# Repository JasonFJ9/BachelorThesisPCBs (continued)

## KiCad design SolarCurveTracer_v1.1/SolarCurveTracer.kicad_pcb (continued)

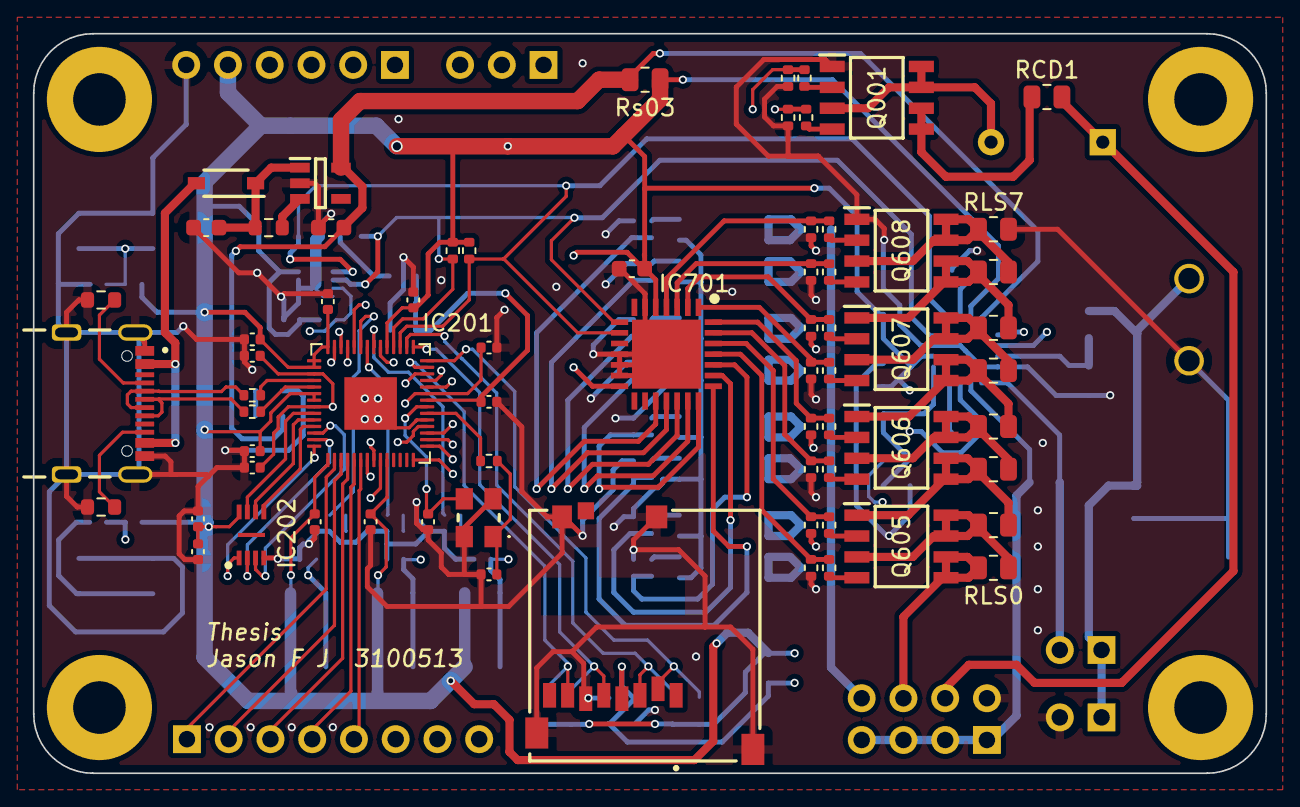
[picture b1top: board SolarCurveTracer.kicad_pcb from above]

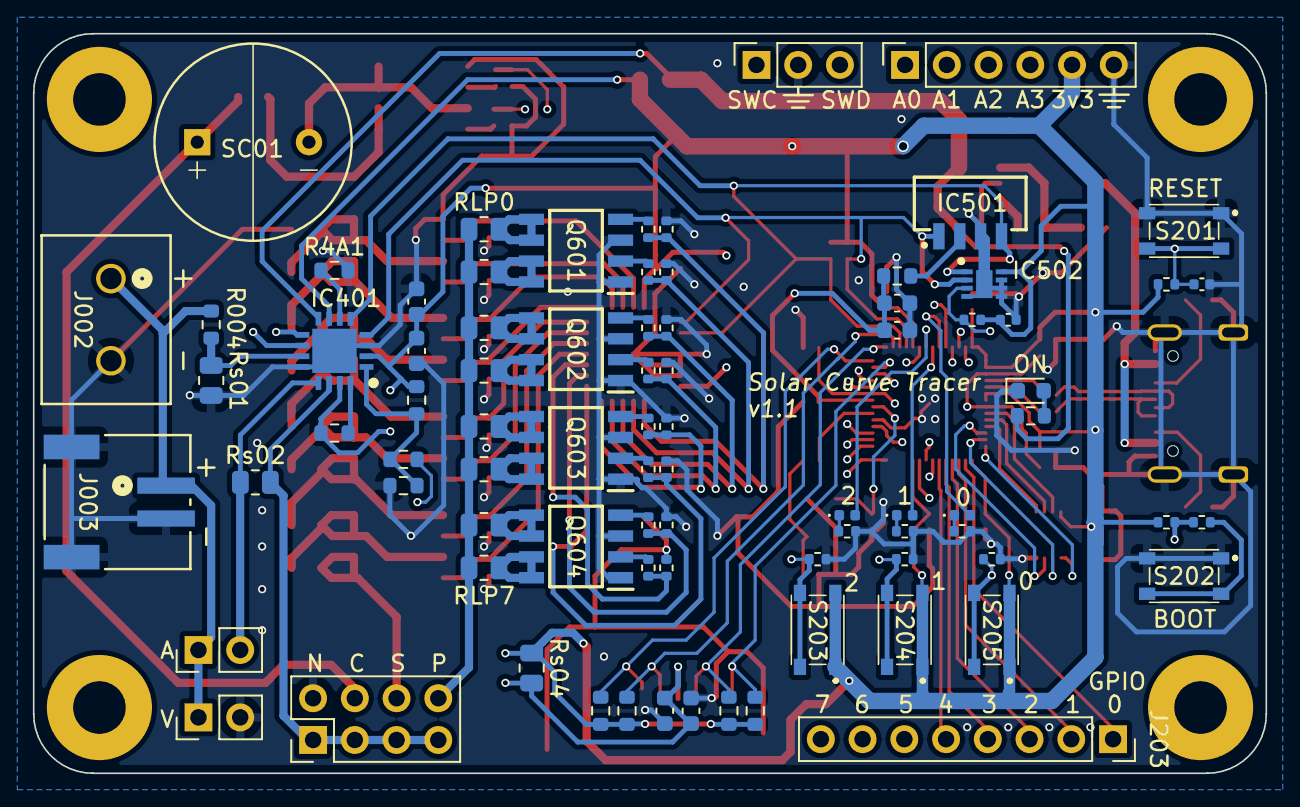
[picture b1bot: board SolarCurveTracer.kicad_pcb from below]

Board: 4 copper layers, 75.0 x 45.0 mm, 154 parts (82 on the bottom side), 120 nets.

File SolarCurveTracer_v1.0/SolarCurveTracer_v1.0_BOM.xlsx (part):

Reference | Value | Footprint | Description | Manufacturer_Part_Number | Mouser Link | DigiKey Link | Qty/Board | Qty/ X Board |  |  |  | X = | 3
AH0-AH2 | JP | Jumper:SolderJumper-2_P1.3mm_Open_TrianglePad1.0x1.5mm | No Need To Order |  | No Need To Order | No Need To Order | 0 | 0 |  |  |  |  | 3
C101, C102 | 1uF | Capacitor_SMD:C_0603_1608Metric |  |  |  |  | 2 | 6 |  |  |  |  | 3
C201, C202 | 15pF | Capacitor_SMD:C_0402_1005Metric | Low Tolerance & High Freq, Changed from 20pF to 15pF |  |  |  | 2 | 6 |  |  |  |  | 3
C203-C208, C211-C213, (C215, C503) | 0.1uF | Capacitor_SMD:C_0402_1005Metric |  |  |  |  | 11 | 33 |  |  |  |  | 3
C209, C210 | 1uF | Capacitor_SMD:C_0402_1005Metric |  |  |  |  | 2 | 6 |  |  |  |  | 3
C214 | 4.7uF | Capacitor_SMD:C_0402_1005Metric |  |  |  |  | 1 | 3 |  |  |  |  | 3
C301, C502 | 10uF | Capacitor_SMD:C_0603_1608Metric |  |  |  |  | 2 | 6 |  |  |  |  | 3
C302, C402, C501, C701 | 0.1uF | Capacitor_SMD:C_0603_1608Metric |  |  |  |  | 4 | 12 |  |  |  |  | 3
C401 | 4.7uF | Capacitor_SMD:C_0603_1608Metric |  |  |  |  | 1 | 3 |  |  |  |  | 3
D101 | B5817W-TP | B5817W-TP:SOD3716X135N |  | B5817W-TP | https://www.mouser.de/ProductDetail/833-B5817W-TP | https://www.digikey.de/en/products/detail/good-ark-semicondu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 | 1 | 3 |  |  |  |  | 3
D201-D203 | LED | LED_SMD:LED_0402_1005Metric |  |  |  |  | 3 | 9 |  |  |  |  | 3
H1-H4 | MountingHole_Pad | MountingHole:MountingHole_3.2mm_M3_Pad | No Need To Order |  | No Need To Order | No Need To Order | 0 | 0 |  |  |  |  | 3
IC101 | AP2112K-3.3TRG1 | AP2112K-3.3TRG1:SOT95P282X130-5N | Mouser Possible Long Lead time | AP2112K-3.3TRG1 | https://www.mouser.de/ProductDetail/Diodes-Incorporated/AP21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 | https://www.digikey.de/de/products/detail/diodes-incorporate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 | 1 | 3 |  |  |  |  | 3
IC201 | RP2040 | Package_DFN_QFN:QFN-56-1EP_7x7mm_P0.4mm_EP3.2x3.2mm |  |  | https://www.mouser.de/ProductDetail/Raspberry-Pi/SC091413?qs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 | https://www.digikey.de/en/products/detail/raspberry-pi/SC091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 | 1 | 3 |  |  |  |  | 3
IC202 | W25Q16JVUXIQ_TR | W25Q16JVUXIQ_TR:SON50P300X200X60-9N |  | W25Q16JVUXIQ TR | https://www.mouser.de/ProductDetail/Winbond/W25Q16JVUXIQ-TR?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 | https://www.digikey.de/en/products/detail/winbond-electronic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 | 1 | 3 |  |  |  |  | 3
IC401 | PAC1934T-I_JQ | PAC1934T-I_JQ:QFN65P400X400X55-17N-D |  | PAC1934T-I/JQ | https://www.mouser.de/ProductDetail/Microchip-Technology/PAC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 | Out of Stock | 1 | 3 |  |  |  |  | 3
IC501 | VEML7700-TT | VEML7700-TT:VEML7700 |  | VEML7700-TT | https://www.mouser.de/ProductDetail/Vishay-Semiconductors/VE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 | https://www.digikey.de/en/products/detail/vishay-semiconduct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 | 1 | 3 |  |  |  |  | 3
IC502 | TMP1075DSGR | TMP1075DSGR:SON50P200X200X80-9N |  | TMP1075DSGR | https://www.mouser.de/ProductDetail/Texas-Instruments/TMP107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 | https://www.digikey.de/en/products/detail/texas-instruments/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 | 1 | 3 |  |  |  |  | 3
IC701 | MCP23017-E_ML | MCP23017-E_ML:QFN65P600X600X100-29N-D |  | MCP23017-E/ML | https://www.mouser.de/ProductDetail/Microchip-Technology/MCP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 | https://www.digikey.de/en/products/detail/microchip-technolo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 | 1 | 3 |  |  |  |  | 3
J001 | Conn_02x04_Odd_Even | Connector_PinHeader_2.54mm:PinHeader_2x04_P2.54mm_Vertical | No Need To Order |  | No Need To Order | No Need To Order | 0 | 0 |  |  |  |  | 3
J002 | 691137710002 | 691137710002:CONN2_710002_WRE |  | 691137710002 | https://www.mouser.de/ProductDetail/Wurth-Elektronik/6911377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 | https://www.digikey.de/en/products/detail/w%C3%BCrth-elektro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 | 1 | 3 |  |  |  |  | 3
J003 | S2B-PH-SM4-TB | S2B_PH_SM4_TB:CONN_S2B-PH-SM4-TB_JST | No Need To Order (In IOT Garage) |  | No Need To Order | No Need To Order | 0 | 0 |  |  |  |  | 3
J004, J005 | Conn_01x02_Pin | Connector_PinHeader_2.54mm:PinHeader_1x02_P2.54mm_Vertical | No Need To Order |  | No Need To Order | No Need To Order | 0 | 0 |  |  |  |  | 3
J101 | USB4105-GF-A | USB4105_GF_A:GCT_USB4105-GF-A |  | USB4105-GF-A | https://www.mouser.de/ProductDetail/GCT/USB4105-GF-A?qs=KUoI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 | https://www.digikey.de/en/products/detail/gct/USB4105-GF-A/11198441 | 1 | 3 |  |  |  |  | 3
J201 | Conn_01x03_Pin | Connector_PinSocket_2.54mm:PinSocket_1x03_P2.54mm_Vertical | No Need To Order |  | No Need To Order | No Need To Order | 0 | 0 |  |  |  |  | 3
J202 | Conn_01x06_Pin | Connector_PinSocket_2.54mm:PinSocket_1x06_P2.54mm_Vertical | No Need To Order |  | No Need To Order | No Need To Order | 0 | 0 |  |  |  |  | 3
J203 | Conn_01x11_Pin | Connector_PinSocket_2.54mm:PinSocket_1x11_P2.54mm_Vertical | No Need To Order |  | No Need To Order | No Need To Order | 0 | 0 |  |  |  |  | 3
J301 | MEM2052-00-195-00-A_REVA | MEM2052-00-195-00-A_REVA:GCT_MEM2052-00-195-00-A_REVA |  | MEM2052-00-195-00-A | https://www.mouser.de/ProductDetail/GCT/MEM2052-00-195-00-A?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 | https://www.digikey.de/en/products/detail/gct/MEM2052-00-195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 | 1 | 3 |  |  |  |  | 3
ON1 | LED | LED_SMD:LED_0603_1608Metric |  |  |  |  | 1 | 3 |  |  |  |  | 3
Q1, Q601-Q608 | SI4204DY-T1-GE3 | SI4204DY-T1-GE3:SOIC127P600X175-8N |  | SI4204DY-T1-GE3 | https://www.mouser.de/ProductDetail/Vishay-Semiconductors/SI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 | https://www.digikey.de/de/products/detail/vishay-siliconix/S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 | 9 | 27 |  |  |  |  | 3
R001-R003 | 4.7kR | Resistor_SMD:R_0402_1005Metric |  |  |  |  | 3 | 9 |  |  |  |  | 3
R004 | 150kR | Resistor_SMD:R_0603_1608Metric | 0603 1% tolerance |  | https://www.mouser.de/ProductDetail/Vishay-Dale/CRCW0603150K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 |  | 1 | 3 |  |  |  |  | 3
R4A1 | 499R | Resistor_SMD:R_0603_1608Metric |  |  |  |  | 1 | 3 |  |  |  |  | 3
R005, R006, R203, R601-R608, R617-R624 | 1kR | Resistor_SMD:R_0402_1005Metric |  |  |  |  | 19 | 57 |  |  |  |  | 3
R007, R008, R209-R212, R609-R616, R625-R632, R701-R703 | 10kR | Resistor_SMD:R_0402_1005Metric |  |  |  |  | 25 | 75 |  |  |  |  | 3
R101, R102 | 5kR | Resistor_SMD:R_0603_1608Metric |  |  |  |  | 2 | 6 |  |  |  |  | 3
R103, R402, R403, R501 | 10kR | Resistor_SMD:R_0603_1608Metric |  |  |  |  | 4 | 12 |  |  |  |  | 3
R104 | 1kR | Resistor_SMD:R_0603_1608Metric |  |  |  |  | 1 | 3 |  |  |  |  | 3
R201, R202 | 27R | Resistor_SMD:R_0402_1005Metric |  |  |  |  | 2 | 6 |  |  |  |  | 3
R204-R206, (R207) | 499R | Resistor_SMD:R_0402_1005Metric |  |  |  |  | 4 | 12 |  |  |  |  | 3
R208 | 2kR | Resistor_SMD:R_0402_1005Metric |  |  |  |  | 1 | 3 |  |  |  |  | 3
R301-R304 | 47kR | Resistor_SMD:R_0603_1608Metric |  |  |  |  | 4 | 12 |  |  |  |  | 3
R404, R405 | 0R | Resistor_SMD:R_0603_1608Metric |  |  |  |  | 2 | 6 |  |  |  |  | 3
RLP4 | 68R | Resistor_SMD:R_0805_2012Metric | 0805 1% tolerance 0.5W |  | https://www.mouser.de/ProductDetail/Vishay-Dale/CRCW080568R0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 |  | 1 | 3 |  |  |  |  | 3
RLP5 | 150R | Resistor_SMD:R_0805_2012Metric | 0805 1% tolerance 0.5W |  | https://www.mouser.de/ProductDetail/Vishay-Dale/CRCW0805150R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 |  | 1 | 3 |  |  |  |  | 3
RLP6 | 330R | Resistor_SMD:R_0805_2012Metric | 0805 1% tolerance 0.5W |  | https://www.mouser.de/ProductDetail/Vishay-Dale/CRCW0805330R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 |  | 1 | 3 |  |  |  |  | 3
RLP7 | 470R | Resistor_SMD:R_0805_2012Metric | 0805 1% tolerance 0.5W |  | https://www.mouser.de/ProductDetail/Vishay-Dale/RCS0805470RF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 |  | 1 | 3 |  |  |  |  | 3
RLS0 | 1R | Resistor_SMD:R_0805_2012Metric | 0805 1% tolerance 0.5W |  | https://www.mouser.de/ProductDetail/Vishay-Dale/RCS08051R00F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 |  | 1 | 3 |  |  |  |  | 3
RLS1 | 2.2R | Resistor_SMD:R_0805_2012Metric | 0805 1% tolerance 0.5W |  | https://www.mouser.de/ProductDetail/Vishay-Dale/CRCW08052R20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 |  | 1 | 3 |  |  |  |  | 3
RLS2 | 4.7R | Resistor_SMD:R_0805_2012Metric | 0805 1% tolerance 0.5W |  | https://www.mouser.de/ProductDetail/Vishay-Dale/CRCW08054R70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 |  | 1 | 3 |  |  |  |  | 3
RLS3, RLP0 | 10R | Resistor_SMD:R_0805_2012Metric | 0805 1% tolerance 0.5W |  | https://www.mouser.de/ProductDetail/Vishay-Dale/CRCW080510R0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 |  | 2 | 6 |  |  |  |  | 3
RLS4, RLP1 | 22R | Resistor_SMD:R_0805_2012Metric | 0805 1% tolerance 0.5W |  | https://www.mouser.de/ProductDetail/Vishay-Dale/RCS080522R0F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 |  | 2 | 6 |  |  |  |  | 3
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
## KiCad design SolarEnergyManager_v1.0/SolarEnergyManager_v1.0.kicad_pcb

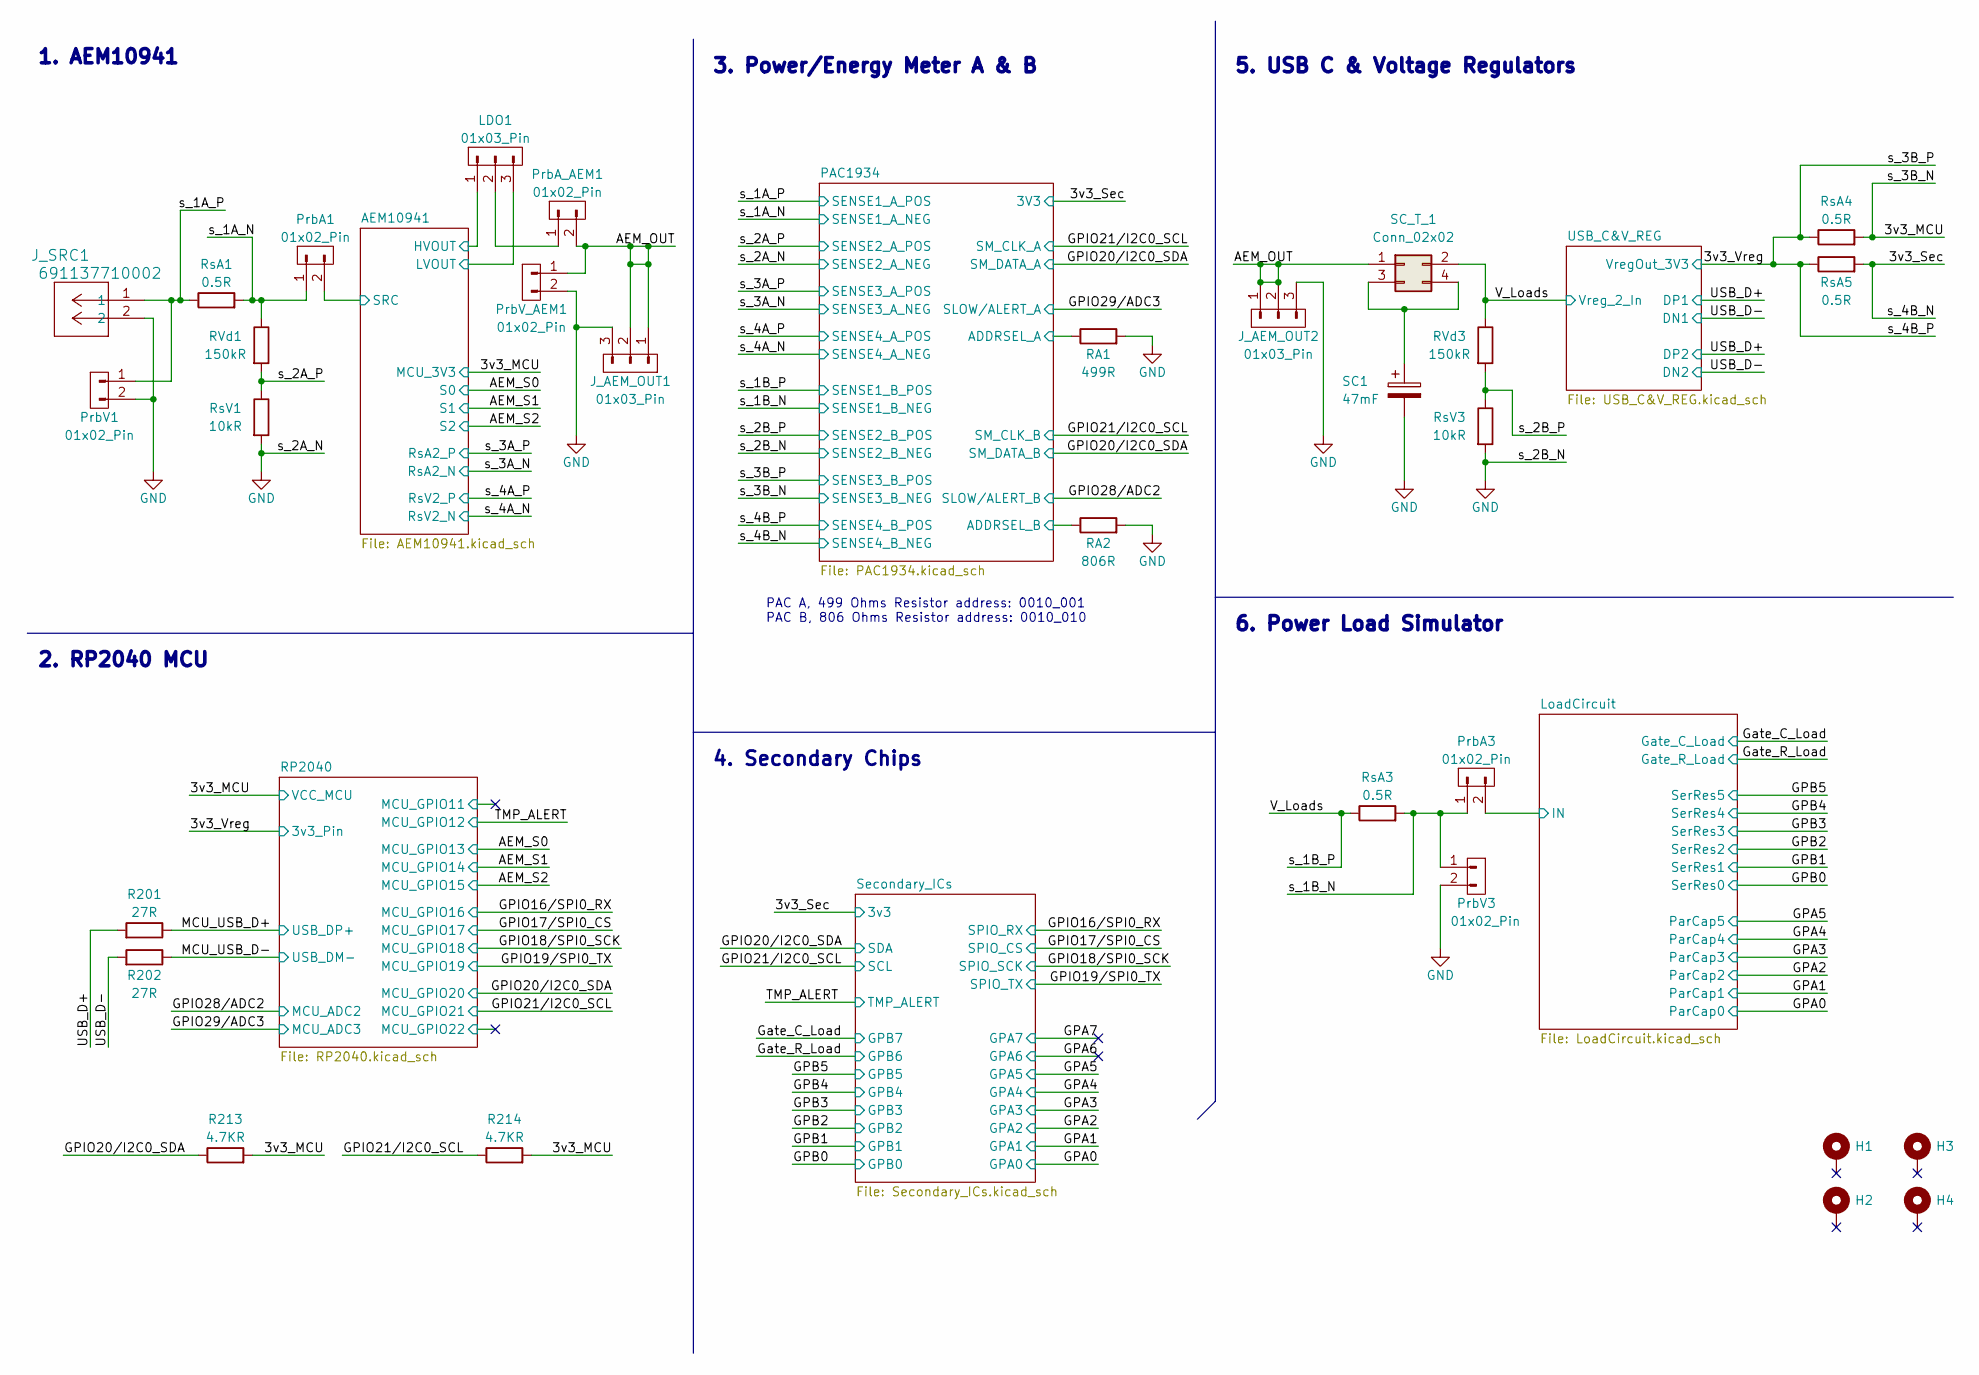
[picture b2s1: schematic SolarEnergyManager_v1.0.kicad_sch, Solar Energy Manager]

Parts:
H1, H2, H3, H4: MountingHole_Pad; MountingHole_3.2mm_M3_Pad
J_AEM_OUT1, J_AEM_OUT2: 01x03_Pin; PinHeader_1x03_P2.54mm_Vertical
J_SRC1: 691137710002; CONN2_710002_WRE
LDO1: 01x03_Pin; PinHeader_1x03_P2.54mm_Vertical
PrbA1, PrbA3: 01x02_Pin; PinHeader_1x02_P2.54mm_Vertical
PrbA_AEM1: 01x02_Pin; PinHeader_1x02_P2.54mm_Vertical
PrbV1, PrbV3: 01x02_Pin; PinHeader_1x02_P2.54mm_Vertical
PrbV_AEM1: 01x02_Pin; PinHeader_1x02_P2.54mm_Vertical
R201, R202: 27R; R_0402_1005Metric
R213, R214: 4.7KR; R_0402_1005Metric
RA1: 499R; R_0402_1005Metric
RA2: 806R; R_0402_1005Metric
RVd1, RVd3: 150kR; R_0402_1005Metric
RsA1, RsA3, RsA4, RsA5: 0.5R; R_0805_2012Metric
RsV1, RsV3: 10kR; R_0402_1005Metric
SC1: 47mF; Capacitor_Radial_D12mm_P6.8mm
SC_T_1: Conn_02x02; PinHeader_2x02_P2.54mm_Vertical

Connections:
/3v3_MCU: R213.2, R214.2, RsA4.2; also elsewhere on the board
/3v3_Sec: RsA5.2; also elsewhere on the board
/3v3_Vreg: RsA4.1, RsA5.1; also elsewhere on the board
/AEM10941/HVOUT: LDO1.1; also elsewhere on the board
/AEM10941/LVOUT: LDO1.3; also elsewhere on the board
/AEM10941/SRC: PrbA1.2; also elsewhere on the board
/AEM_OUT: J_AEM_OUT1.1, J_AEM_OUT1.2, J_AEM_OUT2.1, J_AEM_OUT2.2, PrbA_AEM1.2, PrbV_AEM1.1, SC_T_1.1
/GPIO20/I2C0_SDA: R213.1; also elsewhere on the board
/GPIO21/I2C0_SCL: R214.1; also elsewhere on the board
/LoadCircuit/IN: PrbA3.2; also elsewhere on the board
/MCU_USB_D+: R201.1; also elsewhere on the board
/MCU_USB_D-: R202.1; also elsewhere on the board
/PAC1934/ADDRSEL_A: RA1.1; also elsewhere on the board
/PAC1934/ADDRSEL_B: RA2.1; also elsewhere on the board
/USB_D+: R201.2; also elsewhere on the board
/USB_D-: R202.2; also elsewhere on the board
/V_Loads: RVd3.1, RsA3.1, SC_T_1.2; also elsewhere on the board
/s_1A_N: PrbA1.1, RVd1.1, RsA1.2; also elsewhere on the board
/s_1A_P: J_SRC1.1, PrbV1.1, RsA1.1; also elsewhere on the board
/s_1B_N: PrbA3.1, PrbV3.1, RsA3.2; also elsewhere on the board
/s_2A_P: RVd1.2, RsV1.1; also elsewhere on the board
/s_2B_P: RVd3.2, RsV3.1; also elsewhere on the board
GND: J_AEM_OUT1.3, J_AEM_OUT2.3, J_SRC1.2, PrbV1.2, PrbV3.2, PrbV_AEM1.2, RA1.2, RA2.2, RsV1.2, RsV3.2, SC1.2; also elsewhere on the board
unnamed: LDO1.2, PrbA_AEM1.1
unnamed: SC1.1, SC_T_1.3, SC_T_1.4

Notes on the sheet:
3. Power/Energy Meter A & B
6. Power Load Simulator
5. USB C & Voltage Regulators
2. RP2040 MCU
PAC A, 499 Ohms Resistor address: 0010_001 PAC B, 806 Ohms Resistor address: 0010_010
1. AEM10941
4. Secondary Chips

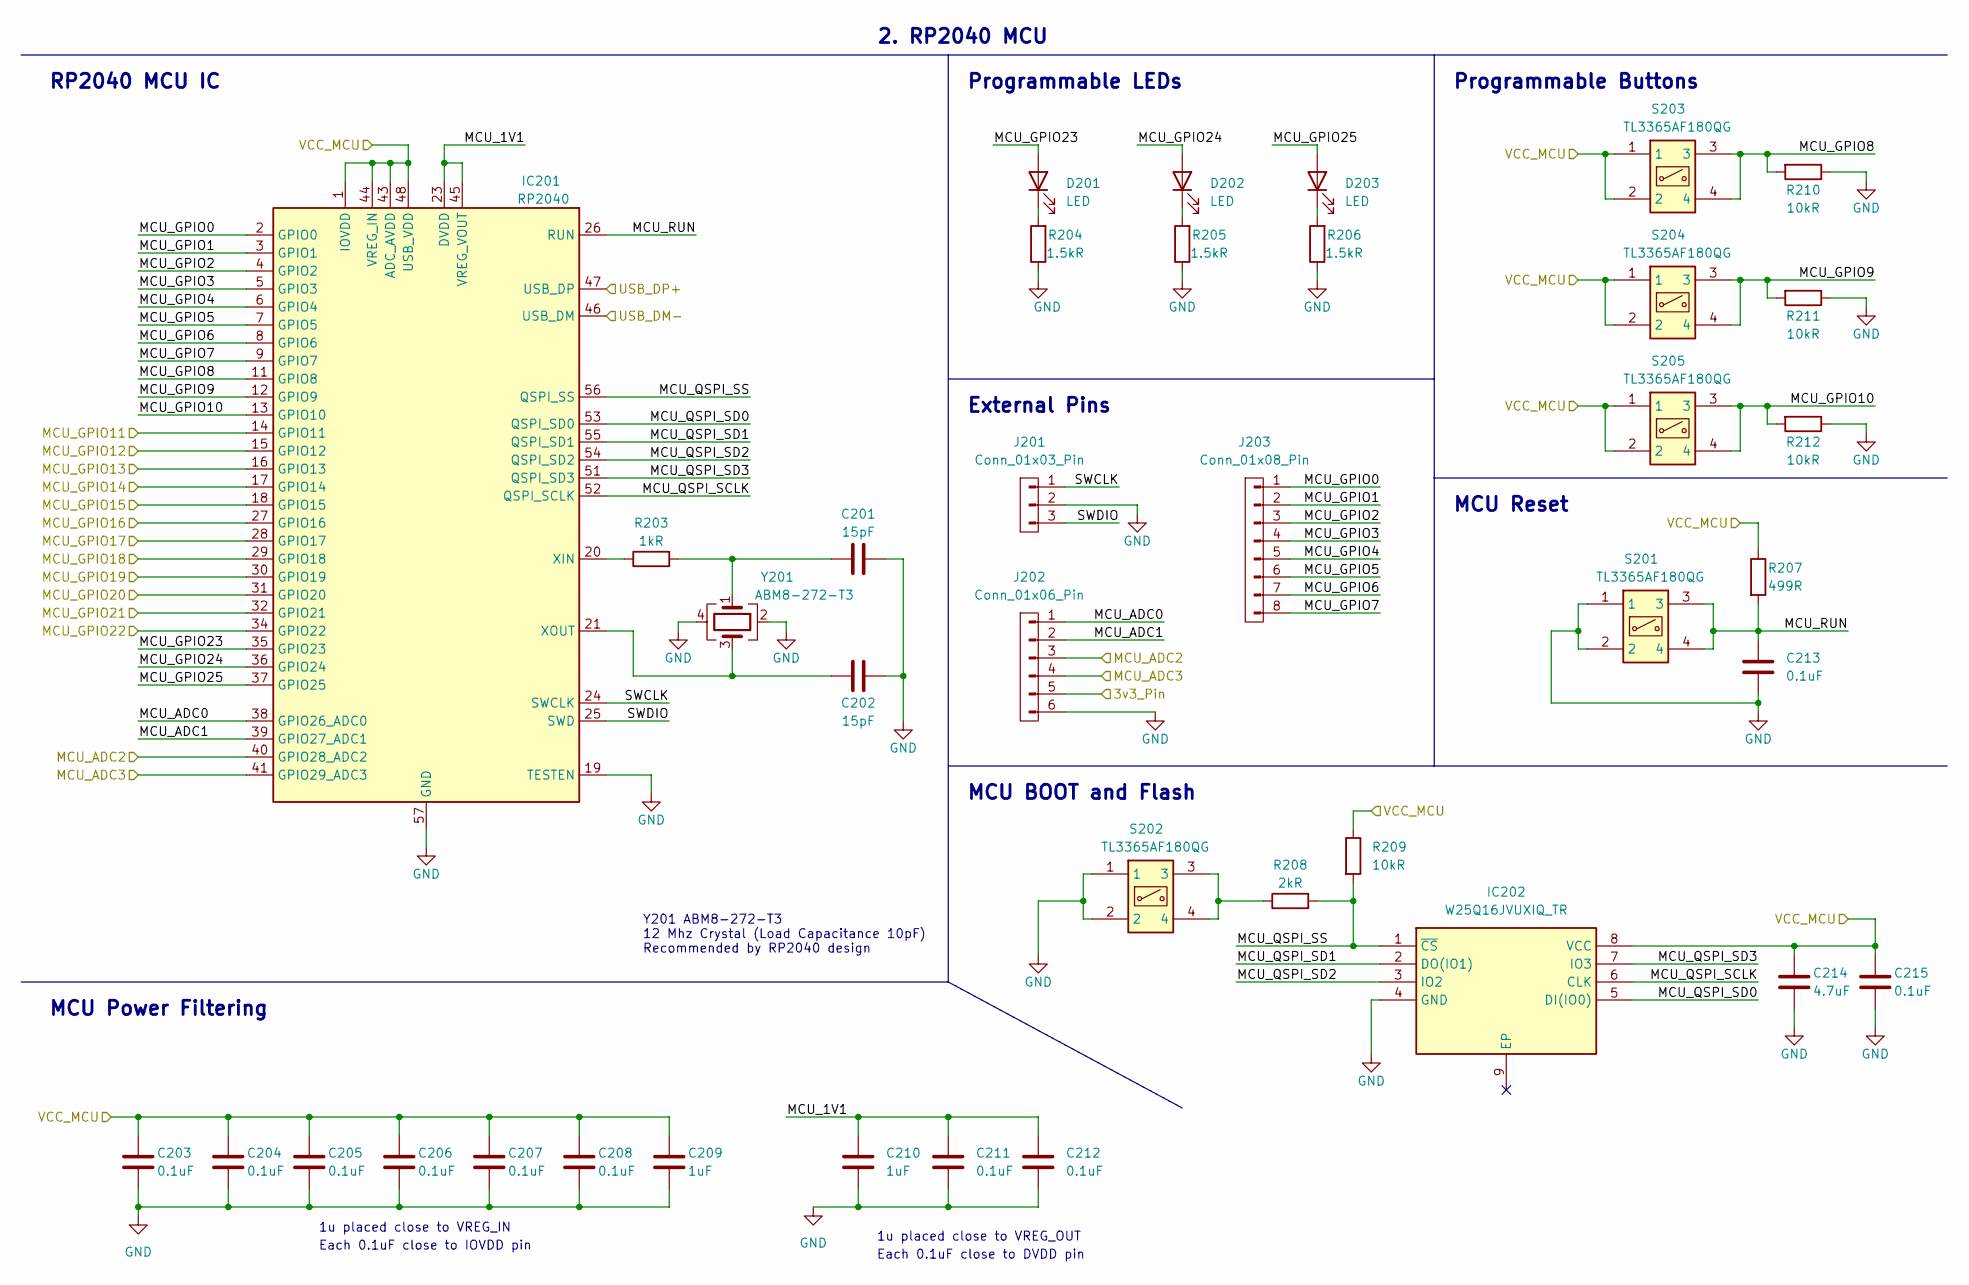
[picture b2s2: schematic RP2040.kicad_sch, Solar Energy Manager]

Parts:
C201, C202: 15pF; C_0402_1005Metric
C203, C204, C205, C206, C207, C208, C211, C212, C213, C215: 0.1uF; C_0402_1005Metric
C209, C210: 1uF; C_0402_1005Metric
C214: 4.7uF; C_0402_1005Metric
D201, D202, D203: LED; LED_0402_1005Metric
IC201: RP2040; QFN-56-1EP_7x7mm_P0.4mm_EP3.2x3.2mm
IC202: W25Q16JVUXIQ_TR; SON50P300X200X60-9N; Mouser Part Number 454-W25Q16JVUXIQTR
J201: Conn_01x03_Pin; PinSocket_1x03_P2.54mm_Vertical
J202: Conn_01x06_Pin; PinSocket_1x06_P2.54mm_Vertical
J203: Conn_01x08_Pin; PinSocket_1x08_P2.54mm_Vertical
R203: 1kR; R_0402_1005Metric
R204, R205, R206: 1.5kR; R_0402_1005Metric
R207: 499R; R_0402_1005Metric
R208: 2kR; R_0402_1005Metric
R209, R210, R211, R212: 10kR; R_0402_1005Metric
S201, S202, S203, S204, S205: TL3365AF180QG; Mouser Part Number 612-TL3365AF180QG
Y201: ABM8-272-T3; ABM8272T3

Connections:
/3v3_MCU: C203.1, C204.1, C205.1, C206.1, C207.1, C208.1, C209.1, C214.1, C215.1, IC201.1 (IOVDD), IC201.10 (IOVDD), IC201.22 (IOVDD), IC201.33 (IOVDD), IC201.42 (IOVDD), IC201.43 (ADC_AVDD), IC201.44 (VREG_IN), IC201.48 (USB_VDD), IC201.49 (IOVDD), IC202.8 (VCC), R207.1, R209.1, S203.1, S203.2, S204.1, S204.2, S205.1, S205.2; also elsewhere on the board
/3v3_Vreg: J202.5; also elsewhere on the board
/AEM_S0: IC201.16 (GPIO13); also elsewhere on the board
/AEM_S1: IC201.17 (GPIO14); also elsewhere on the board
/AEM_S2: IC201.18 (GPIO15); also elsewhere on the board
/GPIO16/SPI0_RX: IC201.27 (GPIO16); also elsewhere on the board
/GPIO17/SPI0_CS: IC201.28 (GPIO17); also elsewhere on the board
/GPIO18/SPI0_SCK: IC201.29 (GPIO18); also elsewhere on the board
/GPIO19/SPI0_TX: IC201.30 (GPIO19); also elsewhere on the board
/GPIO20/I2C0_SDA: IC201.31 (GPIO20); also elsewhere on the board
/GPIO21/I2C0_SCL: IC201.32 (GPIO21); also elsewhere on the board
/GPIO28/ADC2: IC201.40 (GPIO28_ADC2), J202.3; also elsewhere on the board
/GPIO29/ADC3: IC201.41 (GPIO29_ADC3), J202.4; also elsewhere on the board
/MCU_USB_D+: IC201.47 (USB_DP); also elsewhere on the board
/MCU_USB_D-: IC201.46 (USB_DM); also elsewhere on the board
/RP2040/MCU_1V1: C210.1, C211.1, C212.1, IC201.23 (DVDD), IC201.45 (VREG_VOUT), IC201.50 (DVDD)
/RP2040/MCU_ADC0: IC201.38 (GPIO26_ADC0), J202.1
/RP2040/MCU_ADC1: IC201.39 (GPIO27_ADC1), J202.2
/RP2040/MCU_GPIO0: IC201.2 (GPIO0), J203.1
/RP2040/MCU_GPIO1: IC201.3 (GPIO1), J203.2
/RP2040/MCU_GPIO2: IC201.4 (GPIO2), J203.3
/RP2040/MCU_GPIO3: IC201.5 (GPIO3), J203.4
/RP2040/MCU_GPIO4: IC201.6 (GPIO4), J203.5
/RP2040/MCU_GPIO5: IC201.7 (GPIO5), J203.6
/RP2040/MCU_GPIO6: IC201.8 (GPIO6), J203.7
/RP2040/MCU_GPIO7: IC201.9 (GPIO7), J203.8
/RP2040/MCU_GPIO8: IC201.11 (GPIO8), R210.2, S203.3, S203.4
/RP2040/MCU_GPIO9: IC201.12 (GPIO9), R211.2, S204.3, S204.4
/RP2040/MCU_GPIO10: IC201.13 (GPIO10), R212.2, S205.3, S205.4
/RP2040/MCU_GPIO11: IC201.14 (GPIO11)
/RP2040/MCU_GPIO22: IC201.34 (GPIO22)
/RP2040/MCU_GPIO23: D201.2 (A), IC201.35 (GPIO23)
/RP2040/MCU_GPIO24: D202.2 (A), IC201.36 (GPIO24)
/RP2040/MCU_GPIO25: D203.2 (A), IC201.37 (GPIO25)
/RP2040/MCU_QSPI_SCLK: IC201.52 (QSPI_SCLK), IC202.6 (CLK)
/RP2040/MCU_QSPI_SD0: IC201.53 (QSPI_SD0), IC202.5 (DI(IO0))
/RP2040/MCU_QSPI_SD1: IC201.55 (QSPI_SD1), IC202.2 (DO(IO1))
/RP2040/MCU_QSPI_SD2: IC201.54 (QSPI_SD2), IC202.3 (IO2)
/RP2040/MCU_QSPI_SD3: IC201.51 (QSPI_SD3), IC202.7 (IO3)
/RP2040/MCU_QSPI_SS: IC201.56 (QSPI_SS), IC202.1 (~CS), R208.2, R209.2
/RP2040/MCU_RUN: C213.1, IC201.26 (RUN), R207.2, S201.3, S201.4
/RP2040/SWCLK: IC201.24 (SWCLK), J201.1
/RP2040/SWDIO: IC201.25 (SWD), J201.3
/TMP_ALERT: IC201.15 (GPIO12); also elsewhere on the board
GND: C201.2, C202.2, C203.2, C204.2, C205.2, C206.2, C207.2, C208.2, C209.2, C210.2, C211.2, C212.2, C213.2, C214.2, C215.2, IC201.19 (TESTEN), IC201.57 (GND), IC202.4 (GND), J201.2, J202.6, R204.1, R205.1, R206.1, R210.1, R211.1, R212.1, S201.1, S201.2, S202.1, S202.2, Y201.2, Y201.4; also elsewhere on the board
unnamed: C201.1, R203.2, Y201.1
unnamed: D201.1 (K), R204.2
unnamed: D202.1 (K), R205.2
unnamed: D203.1 (K), R206.2
unnamed: IC201.20 (XIN), R203.1
unnamed: C202.1, IC201.21 (XOUT), Y201.3
unnamed: R208.1, S202.3, S202.4

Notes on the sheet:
External Pins
MCU Reset
Each 0.1uF close to DVDD pin
Y201 ABM8-272-T3 12 Mhz Crystal (Load Capacitance 10pF) Recommended by RP2040 design
1u placed close to VREG_OUT
MCU Power Filtering
2. RP2040 MCU
MCU BOOT and Flash
Each 0.1uF close to IOVDD pin
1u placed close to VREG_IN
Programmable Buttons
Programmable LEDs
RP2040 MCU IC

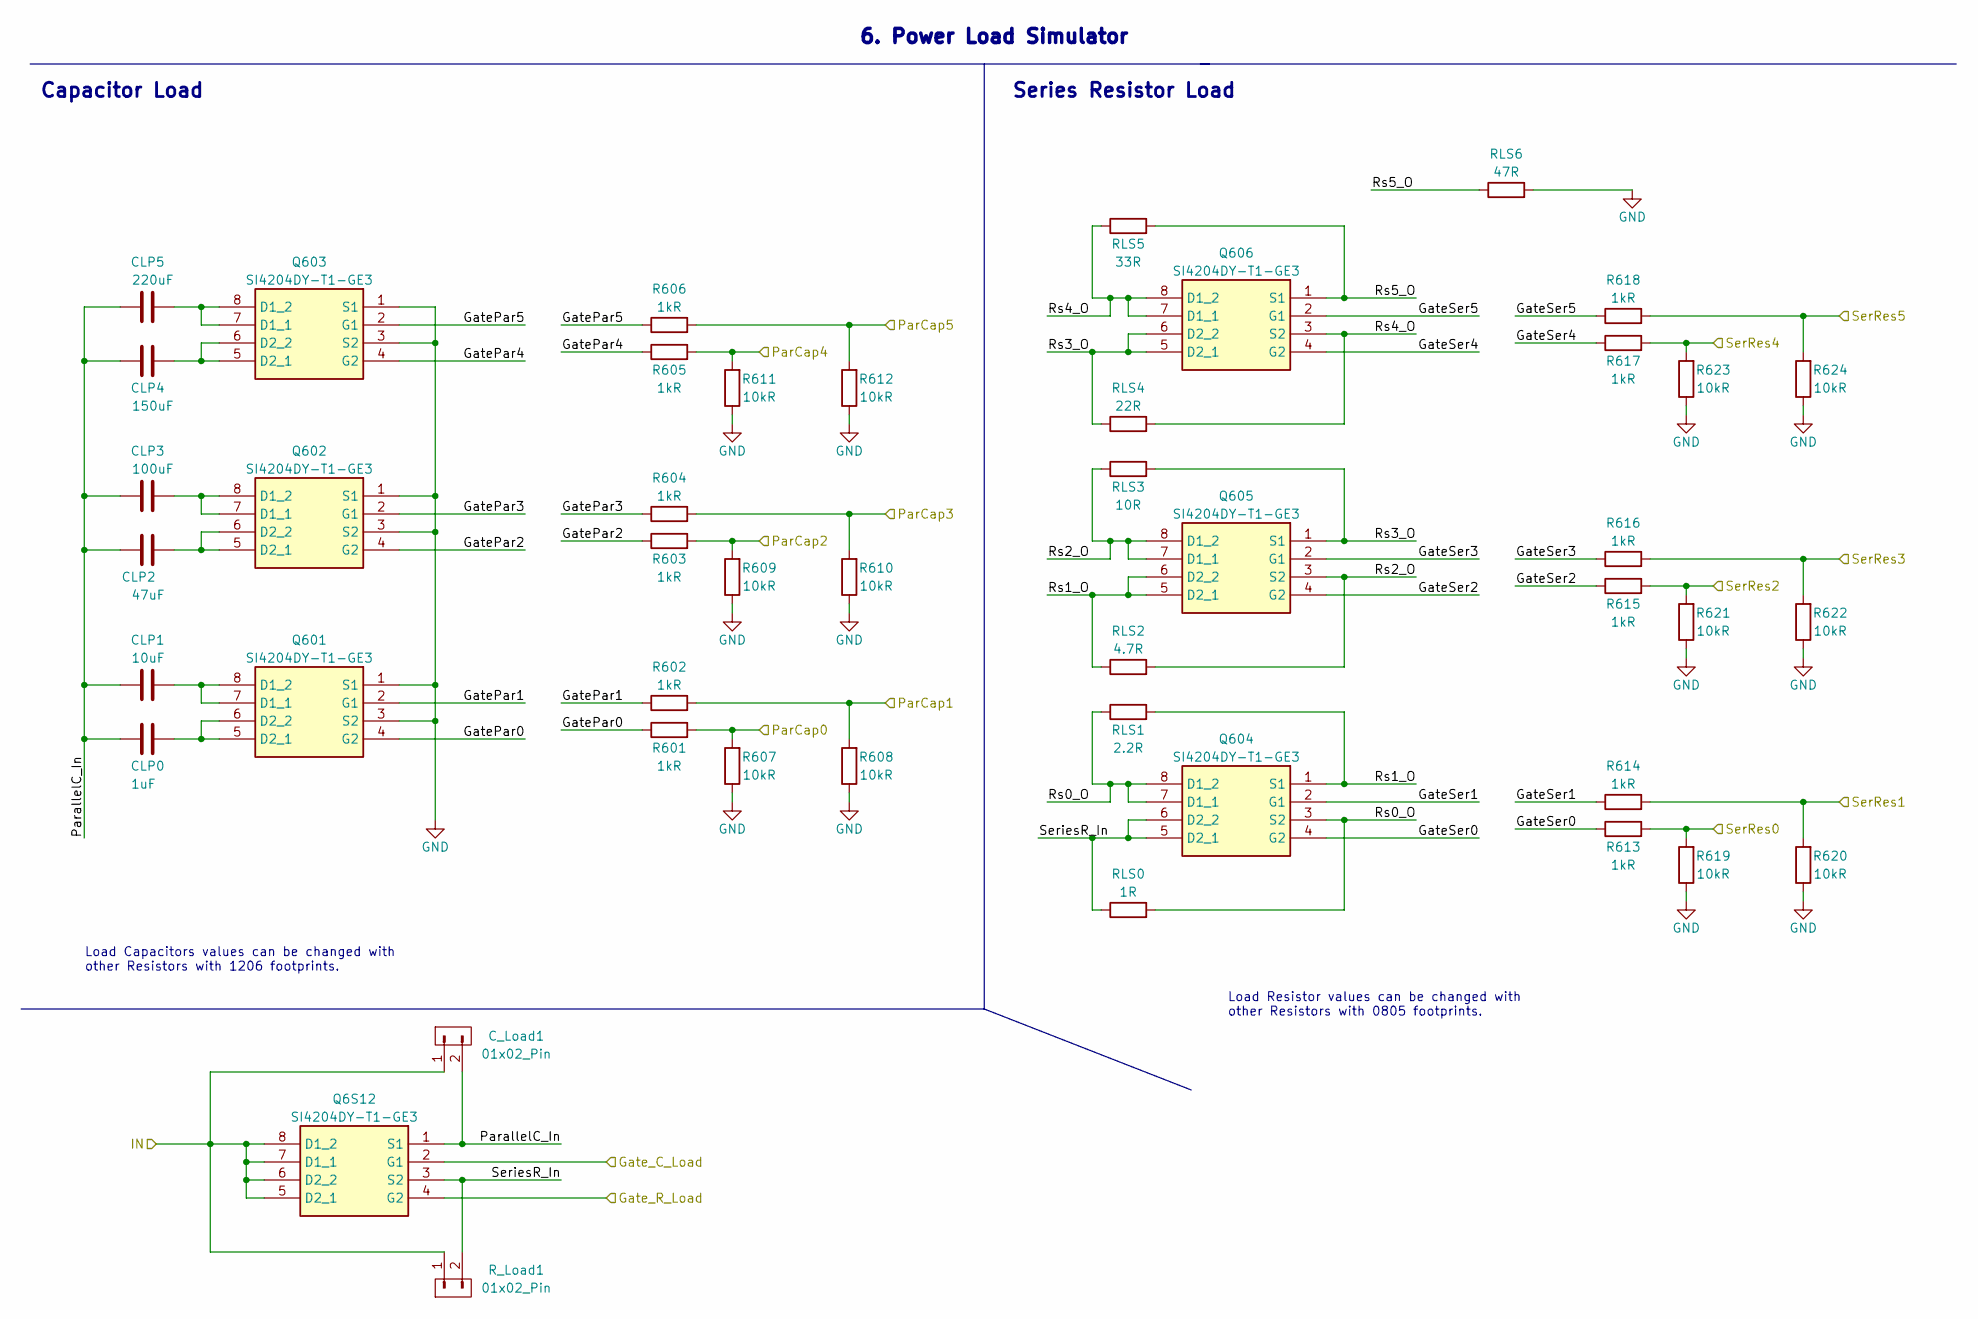
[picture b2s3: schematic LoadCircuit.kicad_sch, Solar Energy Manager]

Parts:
CLP0: 1uF; C_1206_3216Metric
CLP1: 10uF; C_1206_3216Metric
CLP2: 47uF; C_1206_3216Metric
CLP3: 100uF; C_1206_3216Metric
CLP4: 150uF; C_1206_3216Metric
CLP5: 220uF; C_1206_3216Metric
C_Load1: 01x02_Pin; PinHeader_1x02_P2.54mm_Vertical
Q6S12, Q601, Q602, Q603, Q604, Q605, Q606: SI4204DY-T1-GE3; SOIC127P600X175-8N; Mouser Part Number 781-SI4204DY-T1-GE3
R601, R602, R603, R604, R605, R606, R613, R614, R615, R616, R617, R618: 1kR; R_0402_1005Metric
R607, R608, R609, R610, R611, R612, R619, R620, R621, R622, R623, R624: 10kR; R_0402_1005Metric
RLS0: 1R; R_0805_2012Metric
RLS1: 2.2R; R_0805_2012Metric
RLS2: 4.7R; R_0805_2012Metric
RLS3: 10R; R_0805_2012Metric
RLS4: 22R; R_0805_2012Metric
RLS5: 33R; R_0805_2012Metric
RLS6: 47R; R_0805_2012Metric
R_Load1: 01x02_Pin; PinHeader_1x02_P2.54mm_Vertical

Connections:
/GPA0: R601.2, R607.2; also elsewhere on the board
/GPA1: R602.2, R608.2; also elsewhere on the board
/GPA2: R603.2, R609.2; also elsewhere on the board
/GPA3: R604.2, R610.2; also elsewhere on the board
/GPA4: R605.2, R611.2; also elsewhere on the board
/GPA5: R606.2, R612.2; also elsewhere on the board
/GPB0: R613.2, R619.2; also elsewhere on the board
/GPB1: R614.2, R620.2; also elsewhere on the board
/GPB2: R615.2, R621.2; also elsewhere on the board
/GPB3: R616.2, R622.2; also elsewhere on the board
/GPB4: R617.2, R623.2; also elsewhere on the board
/GPB5: R618.2, R624.2; also elsewhere on the board
/Gate_C_Load: Q6S12.2 (G1); also elsewhere on the board
/Gate_R_Load: Q6S12.4 (G2); also elsewhere on the board
/LoadCircuit/GatePar0: Q601.4 (G2), R601.1
/LoadCircuit/GatePar1: Q601.2 (G1), R602.1
/LoadCircuit/GatePar2: Q602.4 (G2), R603.1
/LoadCircuit/GatePar3: Q602.2 (G1), R604.1
/LoadCircuit/GatePar4: Q603.4 (G2), R605.1
/LoadCircuit/GatePar5: Q603.2 (G1), R606.1
/LoadCircuit/GateSer0: Q604.4 (G2), R613.1
/LoadCircuit/GateSer1: Q604.2 (G1), R614.1
/LoadCircuit/GateSer2: Q605.4 (G2), R615.1
/LoadCircuit/GateSer3: Q605.2 (G1), R616.1
/LoadCircuit/GateSer4: Q606.4 (G2), R617.1
/LoadCircuit/GateSer5: Q606.2 (G1), R618.1
/LoadCircuit/IN: C_Load1.1, Q6S12.5 (D2_1), Q6S12.6 (D2_2), Q6S12.7 (D1_1), Q6S12.8 (D1_2), R_Load1.1; also elsewhere on the board
/LoadCircuit/ParallelC_In: CLP0.1, CLP1.1, CLP2.1, CLP3.1, CLP4.1, CLP5.1, C_Load1.2, Q6S12.1 (S1)
/LoadCircuit/Rs0_O: Q604.3 (S2), Q604.7 (D1_1), Q604.8 (D1_2), RLS0.2, RLS1.1
/LoadCircuit/Rs1_O: Q604.1 (S1), Q605.5 (D2_1), Q605.6 (D2_2), RLS1.2, RLS2.1
/LoadCircuit/Rs2_O: Q605.3 (S2), Q605.7 (D1_1), Q605.8 (D1_2), RLS2.2, RLS3.1
/LoadCircuit/Rs3_O: Q605.1 (S1), Q606.5 (D2_1), Q606.6 (D2_2), RLS3.2, RLS4.1
/LoadCircuit/Rs4_O: Q606.3 (S2), Q606.7 (D1_1), Q606.8 (D1_2), RLS4.2, RLS5.1
/LoadCircuit/Rs5_O: Q606.1 (S1), RLS5.2, RLS6.1
/LoadCircuit/SeriesR_In: Q6S12.3 (S2), Q604.5 (D2_1), Q604.6 (D2_2), RLS0.1, R_Load1.2
GND: Q601.1 (S1), Q601.3 (S2), Q602.1 (S1), Q602.3 (S2), Q603.1 (S1), Q603.3 (S2), R607.1, R608.1, R609.1, R610.1, R611.1, R612.1, R619.1, R620.1, R621.1, R622.1, R623.1, R624.1, RLS6.2; also elsewhere on the board
unnamed: CLP1.2, Q601.7 (D1_1), Q601.8 (D1_2)
unnamed: CLP0.2, Q601.5 (D2_1), Q601.6 (D2_2)
unnamed: CLP3.2, Q602.7 (D1_1), Q602.8 (D1_2)
unnamed: CLP2.2, Q602.5 (D2_1), Q602.6 (D2_2)
unnamed: CLP5.2, Q603.7 (D1_1), Q603.8 (D1_2)
unnamed: CLP4.2, Q603.5 (D2_1), Q603.6 (D2_2)

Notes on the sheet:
Series Resistor Load
Load Resistor values can be changed with other Resistors with 0805 footprints.
6. Power Load Simulator
Load Capacitors values can be changed with other Resistors with 1206 footprints.
Capacitor Load
